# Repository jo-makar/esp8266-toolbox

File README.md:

# esp8266-toolbox
Motley of servers, clients and drivers for the ESP8266

# Status
- [ ] HTTP server framework
  - How to practically provide a server while in station-only mode?
  - State-machine design (ie push/pull data with callbacks handled by a task)
- [ ] Over-The-Air updates
  - [ ] RSA signed firmware 
  - [ ] Push updates using HTTP/S server
  - [ ] Pull updates using HTTP/S client (or by holding GPIO0 low x seconds?)
- [x] SMTP client framework
  - [x] CRAM-MD5 authentication
  - [ ] SSL support (via BearSSL or similar)
- [x] Logging framework inspired by syslog
  - [ ] Store entries in a circular buffer (to be sent by SMTP/HTTP)
  - [ ] Use SNTP for timestamps if available
- [ ] Environment monitoring
  - [ ] Ambient light
    - [ ] TLS2561 light sensing
    - [ ] Add interrupt support
  - [ ] Motion, vibration
  - [ ] Temperature, humidity
- [x] Custom board design
- [ ] Battery circuit monitoring
- [ ] Sleep mode for power conservation
- [ ] Self-diagnosis and healing
  - [ ] Monitor heap usage and stack pointer
- [ ] MQTT client framework

# Quick start
- Install the toolchain and SDK: https://github.com/pfalcon/esp-open-sdk
- Modify the Makefile variables in config.mk if necessary
- Modify the WiFi, SMTP, etc constants in config.h for your installation
- Run `make` to build the application binaries
- Power the circuit and connect via a USB-UART bridge
- Put the ESP8266 in flash mode by holding GPIO0 low during boot
- Run `make flash` to flash the application over USB/UART0

# Hardware
This software was intended for use with the common eight-pin ESP-12, though it
will work with any ESP8266 module with only minor modifications.

# SMTP client framework
A simple SMTP client for sending mails and texts is available in smtp/.

Currently only supporting non-SSL/TLS SMTP providers (eg SMTP2GO).

Internally designed using a clean state-machine (ie asynchronously push/pull
data) to conceal the callbacks used by the SDK and simplify porting to other
systems.

However the user interface is purposefully made simple (ie just `launch()` and
`status()`) because the SDK has no mechanism to "release" the processor to run
other tasks/timers, or to put it differently the scheduler only triggers when
nothing else is executing.  Compare this to a typical RTOS where a `delay()` or
`sleep()` function generally triggers rescheduling.

The following shows the user code compared to a simplified view of what happens
internally.

```c
smtp_send_launch("world@internet", "Hello world", NULL);
/* ... */

/* If needed and later after the function calling launch() has returned */
if ((state = smtp_send_status()) == STMP_STATE_ERROR)
    /* Handle error */
else if (state == SMTP_STATE_RESOLVE)
    /* Still resolving SMTP server host */
/* ... */
```

```c
struct {
    int8_t state;
    /* ... */
    os_timer_t timer;
} smtp_state;

ICACHE_FLASH_ATTR void smtp_send_launch(const char *to, const char *subj,
                                        const char *body) {
    /* Validate and buffer input */

    smtp_state.state = SMTP_STATE_READY;
    smtp_handler(NULL);
}

ICACHE_FLASH_ATTR void smtp_handler(void *arg) {
    if (smtp_state.state == SMTP_STATE_ERROR) {
        /* Handle error */
        return;
    }

    else if (smtp_state.state == SMTP_STATE_READY) {
        /* Start process */
        smtp_state.state = SMTP_STATE_RESOLVE;
    }

    else if (smtp_state.state == SMTP_STATE_RESOLVE) {
        /* Launch SMTP server hostname resolution */
    }

    else if (smtp_state.state == SMTP_STATE_CONNECT) {
        /* Connect to the SMTP server */
    }

    /* ... */

    /* Schedule an execution of itself in three seconds */
    os_timer_disarm(&smtp_state.timer);
    os_timer_setfn(&smtp_state.timer, smtp_handler, NULL);
    os_timer_arm(&smtp_state.timer, 1000*3, false);
}
```

# Logging framework
A logging framework akin to Linux's syslog(3) is available via log.h.

An example use case from user_init.c:

`log_info("main", "version %s built on %s", VERSION, BUILD_DATETIME);`

Will produce a log entry similar to the following:

`00:00:15.506: info: user_init.c:13: version 1.0.0 built on Aug 10 2017 06:52:39`

Which is comprised of the system time (hours:minutes:seconds.milliseconds), log
level, file path and line number and finally entry proper.

The log entries are sent to UART0 (with the default baudrate and params).

Run `make uart0` to execute a host application that will read the output
produced from UART0 including the generated log entries. The host application
is provided to support USB-UART bridges that can use non-standard baudrates only
via ioctl() calls, eg the CP2104.

# Custom board design
A simple, two-layer breakout board was designed to simplify development, the
schematic and gerbers are located in board/.

The headers provided are intended to support attaching external boards for
sensors or actuators which are to be interfaced by multiplexing the available
pins (eg TX, RX, GPIO0 and GPIO2).

# License
This software is freely available for non-commerical use, commerical use requires
an expressed agreement from the author. The preceding clause must be included in
all derivative software developed with commerical rights retained by the author
of this software.

The author takes no responsibility for the consequences of the use of this
software.

Use of the software in any form indicates acknowledgement of the licensing terms.

Copyright (c) 2017 J. O. Makar <jomakar@gmail.com>

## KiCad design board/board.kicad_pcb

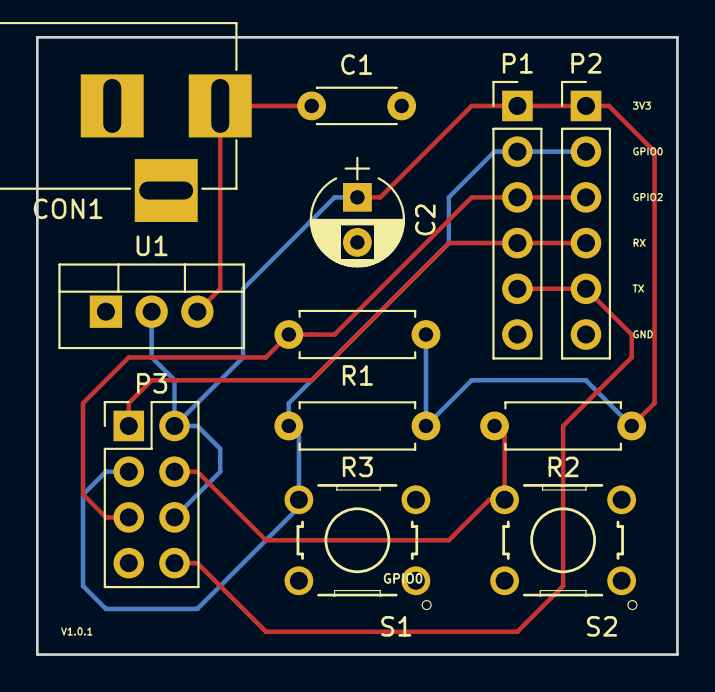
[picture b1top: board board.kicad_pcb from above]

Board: 2 copper layers, 35.6 x 34.3 mm, 12 parts (0 on the bottom side), 8 nets.

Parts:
C1: 10nF; C_Disc_D4.3mm_W1.9mm_P5.00mm
C2: 10uF; CP_Radial_D5.0mm_P2.50mm
CON1: BARREL_JACK
P1, P2: CONN_01X06; Pin_Header_Straight_1x06_Pitch2.54mm
P3: CONN_02X04; Pin_Header_Straight_2x04_Pitch2.54mm
R1, R2, R3: 10K; R_Axial_DIN0207_L6.3mm_D2.5mm_P7.62mm_Horizontal
S1, S2: B3F-1000; SW_B3F-1000
U1: LD1117V33; TO-220_Vertical

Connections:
+3V3: C2.1, P1.1, P2.1, P3.2, P3.6, R1.1, R2.1, R3.1, U1.2
/GPIO0: P1.2, P2.2, P3.3, R3.2, S1.4
/GPIO2: P1.3, P2.3, P3.5, R1.2
/RESET: P3.4, R2.2, S2.4
/RX: P1.4, P2.4, P3.1
/TX: P1.5, P2.5, P3.8
GND: C1.2, C2.2, CON1.2, P1.6, P2.6, P3.7, S1.2, S2.2, U1.1
VCC: C1.1, CON1.1, U1.3

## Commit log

2016-05-11 Real initial commit
2016-05-11 Build changes in anticipation of OTA
2016-05-11 First phase of HTTP-based network config
2016-05-11 Second phase of HTTP-based network config
2016-05-11 Preliminary HTTP-based network config complete
2016-05-11 Added Python reference MQTT implementations
2016-05-20 Added initial MQTT packet handling framework
2016-05-23 Added reconnects and pings to MQTT framework
2016-05-23 Added MQTT publishing
2016-05-25 Fixed MQTT Remaining length field processing
2016-05-26 Fixed MQTT Remaining length field processing redux
2017-07-09 Refactor phase 1
2017-07-11 Refactor baseline
2017-07-12 Added dev schematic
2017-07-12 Minor README.md change
2017-07-12 Removed ICACHE_FLASH_ATTR references since no longer necessary
2017-07-14 Added basic wifi initialization
2017-07-14 Use MACSTR & MAC2STR
2017-07-14 Added httpd framework
2017-07-20 Further httpd framework
2017-07-20 Added ioctl-based baud app
2017-07-20 Updated schematic
2017-07-20 Completed httpd init framework
2017-07-21 Httpd init framework fixes
2017-07-21 Rearrangement of httpd framework
2017-07-21 Started httpd process framework
2017-07-21 Added httpd logging scaffold
2017-07-21 Added general logging scaffold
2017-07-21 Completed initial httpd framework
2017-07-21 Shift httpd post data processing
2017-07-22 Added ICACHE_FLASH_ATTRs
2017-07-22 Update to max conn constants
2017-07-22 Changed httpd post data processing
2017-07-22 HTTP POST FOTA framework complete
2017-07-23 Initial SHA256 implementation
2017-07-23 Added improved logging
2017-07-23 Updated FOTA POST data framework
2017-07-25 Completed FOTA POST framework
2017-07-25 Updated logging framework
2017-07-26 Added system_get_time() overflow handler
2017-07-26 Added /version and /uptime
2017-07-27 Added RSA key parser
2017-07-27 Convert RSA pubkey components to Bigints
2017-07-27 Added bigint_fromhex()
2017-07-28 Further bigint impl work
2017-07-31 Further bigint implementation
2017-08-01 Bigint implementation fixes
2017-08-03 Finalized Bigint implementation
2017-08-04 Added binary signing
2017-08-04 Implemented RSA
2017-08-05 Signed OTA updates completed
2017-08-05 Use the different linker scripts for the two binaries
2017-08-05 Updated the Makefile target fota
2017-08-06 Added /wifi/setup
2017-08-06 Completed /wifi/setup
2017-08-06 Minor fixes
2017-08-06 Log functions refactor phase 1
2017-08-06 Log function refactor completed
2017-08-06 Added /logs
2017-08-06 Minor change to /logs
2017-08-06 Added more logging systems
2017-08-06 Updated log levels
2017-08-07 Added /reset
2017-08-07 Added beginnings of SMTP framework
2017-08-07 Continued work on SMTP framework
2017-08-08 Improved log timestamps
2017-08-09 Further work on SMTP framework
2017-08-09 Switch from http to https
2017-08-10 Finished logging framework
2017-08-11 Finished http framework
2017-08-11 Finished OTA updates
2017-08-11 Started SMTP framework
2017-08-11 Minor changes
2017-08-12 Added url_decode()
2017-08-13 Further SMTP framework
2017-08-14 Finished prelim SMTP framework
2017-08-14 SMTP framework additions
2017-08-15 Minor logging framework fix
2017-08-19 Url decoding fix
2017-08-20 SMTP greeting fix
2017-08-21 Minor SMTP fix
2017-08-22 Added an MD5 implementation
2017-08-22 Added base64 decoding
2017-08-22 Prelim CRAM-MD5 implementation
2017-08-23 Fixed SMTP CRAM-MD5 authentication
2017-08-25 Added TSL2561 (light) driver
2017-08-29 Added v1.0.0 board
2017-08-30 Added board v1.0.1
2017-09-06 Removed bearssl-0.5
2017-09-06 Renamed board/gerber
2017-09-06 Removed crypto
2017-09-06 Removed drivers
2017-09-06 Moved uart0
2017-09-06 Removed log
2017-09-06 Removed http
2017-09-06 Added log.{c,h}
2017-09-06 Modified Makefile
2017-09-06 Modified uptime.{c,h}
2017-09-06 Modified README.md
2017-09-06 Removed smtp
2017-09-06 Removed param.{c,h}
2017-09-06 Modified wifi.c
2017-09-06 Modified config.h
2017-09-06 Fixed buffer use
2017-10-24 Beginnings of smtp client
2017-10-24 Updated .gitignore
2017-10-25 Added smtp framework
2017-10-29 Added to smtp framework
2017-10-30 Completed smtp framework
